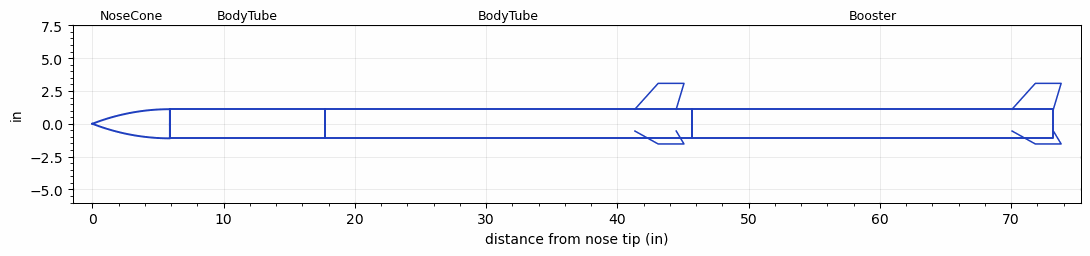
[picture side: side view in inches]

<RASAeroDocument>
 <FileVersion>2</FileVersion>
 <RocketDesign>
  <NoseCone>
   <Length>5.9055</Length>
   <Diameter>2.2205</Diameter>
   <Shape>Tangent Ogive</Shape>
   <Location>0</Location>
  </NoseCone>
  <BodyTube>
   <Length>11.811</Length>
   <Diameter>2.2205</Diameter>
   <Location>5.9055</Location>
  </BodyTube>
  <BodyTube>
   <Length>27.9527</Length>
   <Diameter>2.2205</Diameter>
   <Location>17.7165</Location>
   <Fin>
    <Count>3</Count>
    <Chord>3.1496</Chord>
    <Span>1.9685</Span>
    <SweepDistance>1.7716</SweepDistance>
    <TipChord>1.9685</TipChord>
    <Thickness>0.0787</Thickness>
    <Location>4.3307</Location>
    <AirfoilSection>Rounded</AirfoilSection>
   </Fin>
  </BodyTube>
  <Booster>
   <Length>27.559</Length>
   <Diameter>2.2205</Diameter>
   <InsideDiameter>2.2205</InsideDiameter>
   <Location>45.6692</Location>
   <ShoulderLength>0</ShoulderLength>
   <Fin>
    <Count>3</Count>
    <Chord>3.1496</Chord>
    <Span>1.9685</Span>
    <SweepDistance>1.7716</SweepDistance>
    <TipChord>1.9685</TipChord>
    <Thickness>0.0787</Thickness>
    <Location>3.1496</Location>
    <AirfoilSection>Rounded</AirfoilSection>
   </Fin>
  </Booster>
  <Surface>Camouflage Paint</Surface>
  <ModifiedBarrowman>False</ModifiedBarrowman>
  <Turbulence>False</Turbulence>
  <UseBooster1>True</UseBooster1>
  <UseBooster2>False</UseBooster2>
  <Comments>Try and get high with L2, using the larger end of the motors possible. Now trying with a larger upper stage. Change recovery to ballistic chute deploy.</Comments>
 </RocketDesign>
 <LaunchSite>
  <Altitude>2065</Altitude>
  <Pressure>24.67</Pressure>
  <RodAngle>0</RodAngle>
  <RodLength>10</RodLength>
  <Temperature>80</Temperature>
  <WindSpeed>4.47</WindSpeed>
 </LaunchSite>
 <Recovery>
  <Altitude1>3280.84</Altitude1>
  <Altitude2>3280.84</Altitude2>
  <DeviceType1>Parachute</DeviceType1>
  <DeviceType2>Parachute</DeviceType2>
  <Event1>True</Event1>
  <Event2>True</Event2>
  <Size1>24</Size1>
  <Size2>24</Size2>
  <EventType1>Altitude</EventType1>
  <EventType2>Apogee</EventType2>
  <CD1>0.97</CD1>
  <CD2>0</CD2>
 </Recovery>
 <SimulationList>
  <Simulation>
   <SustainerEngine>L265-MY-P  (CTI)</SustainerEngine>
   <SustainerLaunchWt>6.65</SustainerLaunchWt>
   <SustainerCG>30.9</SustainerCG>
   <SustainerIgnitionDelay>18</SustainerIgnitionDelay>
   <Booster1Engine>K570  (CTI)</Booster1Engine>
   <Booster1LaunchWt>11.17</Booster1LaunchWt>
   <Booster1SeparationDelay>10</Booster1SeparationDelay>
   <Booster1IgnitionDelay>0</Booster1IgnitionDelay>
   <Booster1CG>43.74</Booster1CG>
   <IncludeBooster1>True</IncludeBooster1>
   <Booster2Delay>0</Booster2Delay>
   <IncludeBooster2>False</IncludeBooster2>
   <TimetoApogee>29.79049</TimetoApogee>
   <MaxAltitude>15505.9</MaxAltitude>
   <MaxVelocity>566.886</MaxVelocity>
  </Simulation>
 </SimulationList>
</RASAeroDocument>
